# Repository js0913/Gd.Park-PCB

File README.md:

# Gd.Park-PCB
 My very first keyboard PCB!

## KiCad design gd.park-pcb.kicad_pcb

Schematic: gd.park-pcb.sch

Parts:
C1: 01.uF; C_0805_2012Metric
C2, C3: 0.1uF; C_0805_2012Metric
C4: 10uF; C_0805_2012Metric
C5, C6: 22pF; C_0805_2012Metric
C7: 1uF; C_0805_2012Metric
D1, D2, D3, D4: SOD-123; D_SOD-123
F1: 500mA; Fuse_1206_3216Metric
MX1, MX2, MX3, MX4: MX-NoLED; MX-1U-NoLED
R1, R2: 22; R_0805_2012Metric
R3, R4: 10k; R_0805_2012Metric
SW1: SW_Push; SKQG-1155865
U1: ATmega32U4-AU; TQFP-44_10x10mm_P0.8mm
USB1: Molex-0548190589
Y1: 16MHz; Crystal_SMD_3225-4Pin_3.2x2.5mm

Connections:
+5V: C1.1, C2.1, C3.1, C4.1, F1.1, R3.1, U1.2 (UVCC), U1.7 (VBUS), U1.14 (VCC), U1.24 (AVCC), U1.34 (VCC), U1.44 (AVCC)
COL0: MX1.1, MX2.1, U1.29 (PB5)
COL1: MX3.1, MX4.1, U1.28 (PB4)
D+: R2.2, USB1.3 (D+)
D-: R1.2, USB1.4 (D-)
GND: C1.2, C2.2, C3.2, C4.2, C5.2, C6.2, C7.2, R4.1, SW1.1, U1.5 (UGND), U1.15 (GND), U1.23 (GND), U1.35 (GND), U1.43 (GND), USB1.1 (GND), Y1.1, Y1.3
unnamed: C5.1, U1.17 (XTAL1), Y1.4
unnamed: C6.1, U1.16 (XTAL2), Y1.2
unnamed: C7.1, U1.6 (UCAP)
unnamed: D1.2, MX1.2
unnamed: D2.2, MX2.2
unnamed: D3.2, MX3.2
unnamed: D4.2, MX4.2
unnamed: R1.1, U1.3 (D-)
unnamed: R2.1, U1.4 (D+)
unnamed: R3.2, SW1.2, U1.13 (~RESET)
unnamed: R4.2, U1.33 (~HWB~/PE2)
ROW0: D1.1, D3.1, U1.27 (PD7)
ROW1: D2.1, D4.1, U1.30 (PB6)
VCC: F1.2, USB1.5 (VBUS)

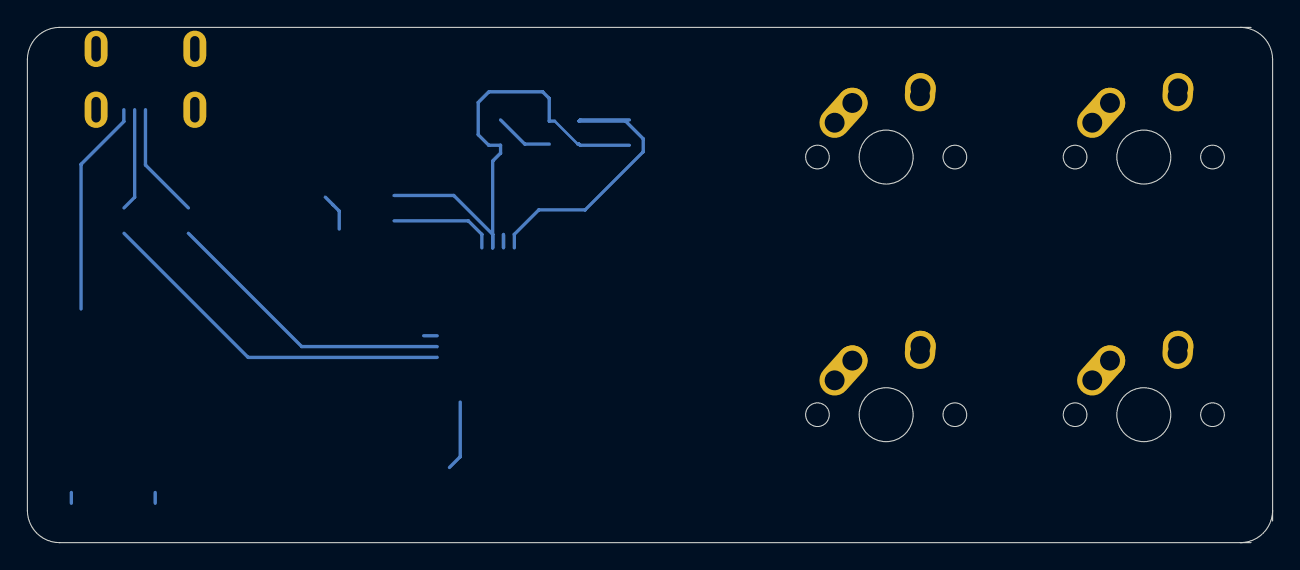
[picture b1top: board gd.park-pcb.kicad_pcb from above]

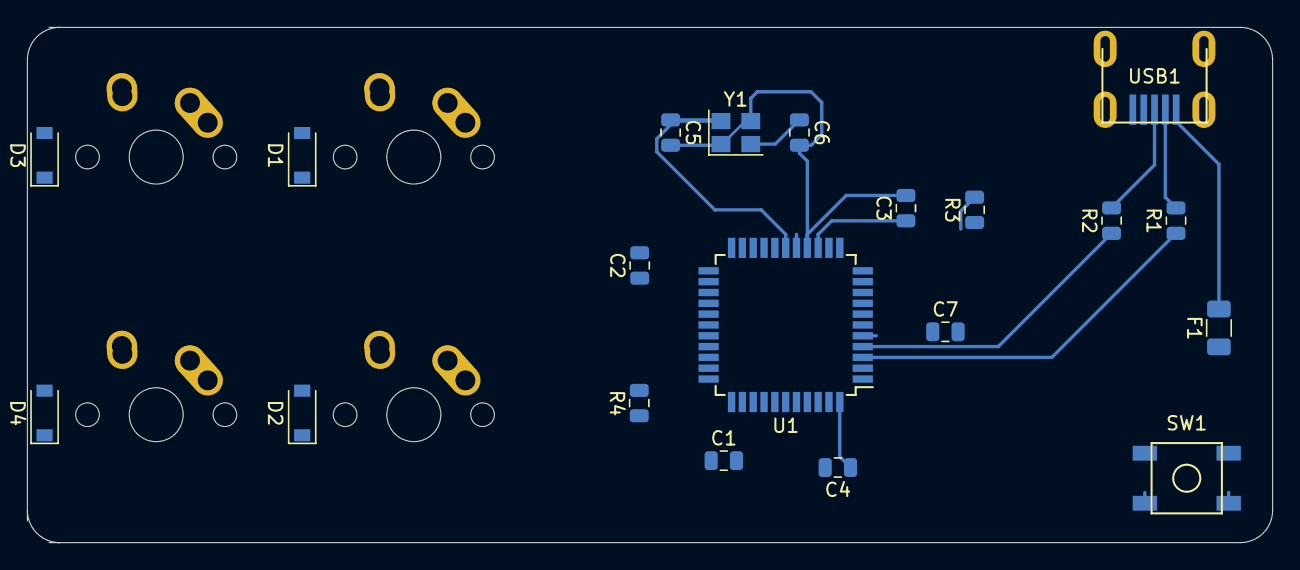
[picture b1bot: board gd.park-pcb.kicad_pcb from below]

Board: 2 copper layers, 92.1 x 38.1 mm, 24 parts (20 on the bottom side), 20 nets.

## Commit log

2021-11-13 Start!
2021-11-13 Add submodules
2021-11-13 Add footprint libraries
2021-11-13 ing..
